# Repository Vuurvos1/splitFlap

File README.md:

<h1 align="center">SplitFlap</h1>

<p align="center">A modernized split flap display.</p>

## Features

- 50 Flaps per module
- 54mm x 80mm Character size
- Compact 80mm x 160mm x 110mm module size
- 3D printable
- Daisy chained
- Web controllabe

## Dashboard

The display can be controlled through a web dashboard hosted on the controller module.

## Flap Characters

Suggested 50 characters:

```
A B C D E F G H I J K L M N O P Q R S T U V W X Y Z (26)
1 2 3 4 5 6 7 8 9 0 (10)
blank □ full ■ (2)
? ! + - = * ' : , . @ # % € (14)
```

 <!-- $ & ^ ; -->

> [!NOTE]  
> `0 O` and `1 I` can share the same flap

## Materials

- 1x Nema 17 Stepper Motor
- 1x A4988 Stepper Motor Driver (or similar)
- 1x Hall Effect Switch (a TLE4905L or similar)
- 8x M3 Countersunk Screws (for the body)
- 8x M3 Screws (for the barrel)
- 4x M3x18 Screws (to mount the motor)
- 1x M3 Countersunk Screw (for the flap stopper)

### Micro controller

- Esp32
- Arduino pro micro

I am using an Esp32 for the main module, and you can use any other micro controller like a pro micro for the other modules.

### Motor

I originally got dual shafted Nema 17 motors for this project so I could mount the flap barrel on the back side of the motor.

> [!NOTE]  
> You could use any other Nema 17 motor with a reversed D shaft.
> Reversing the shaft can easily be done if you open up the motor and flip the shaft so it sticks out of the "back" of the motor.
> You might need to tweak the motor spacers and use different length screws to mount different motors.

### Driver

- A4988 Stepper Motor Driver

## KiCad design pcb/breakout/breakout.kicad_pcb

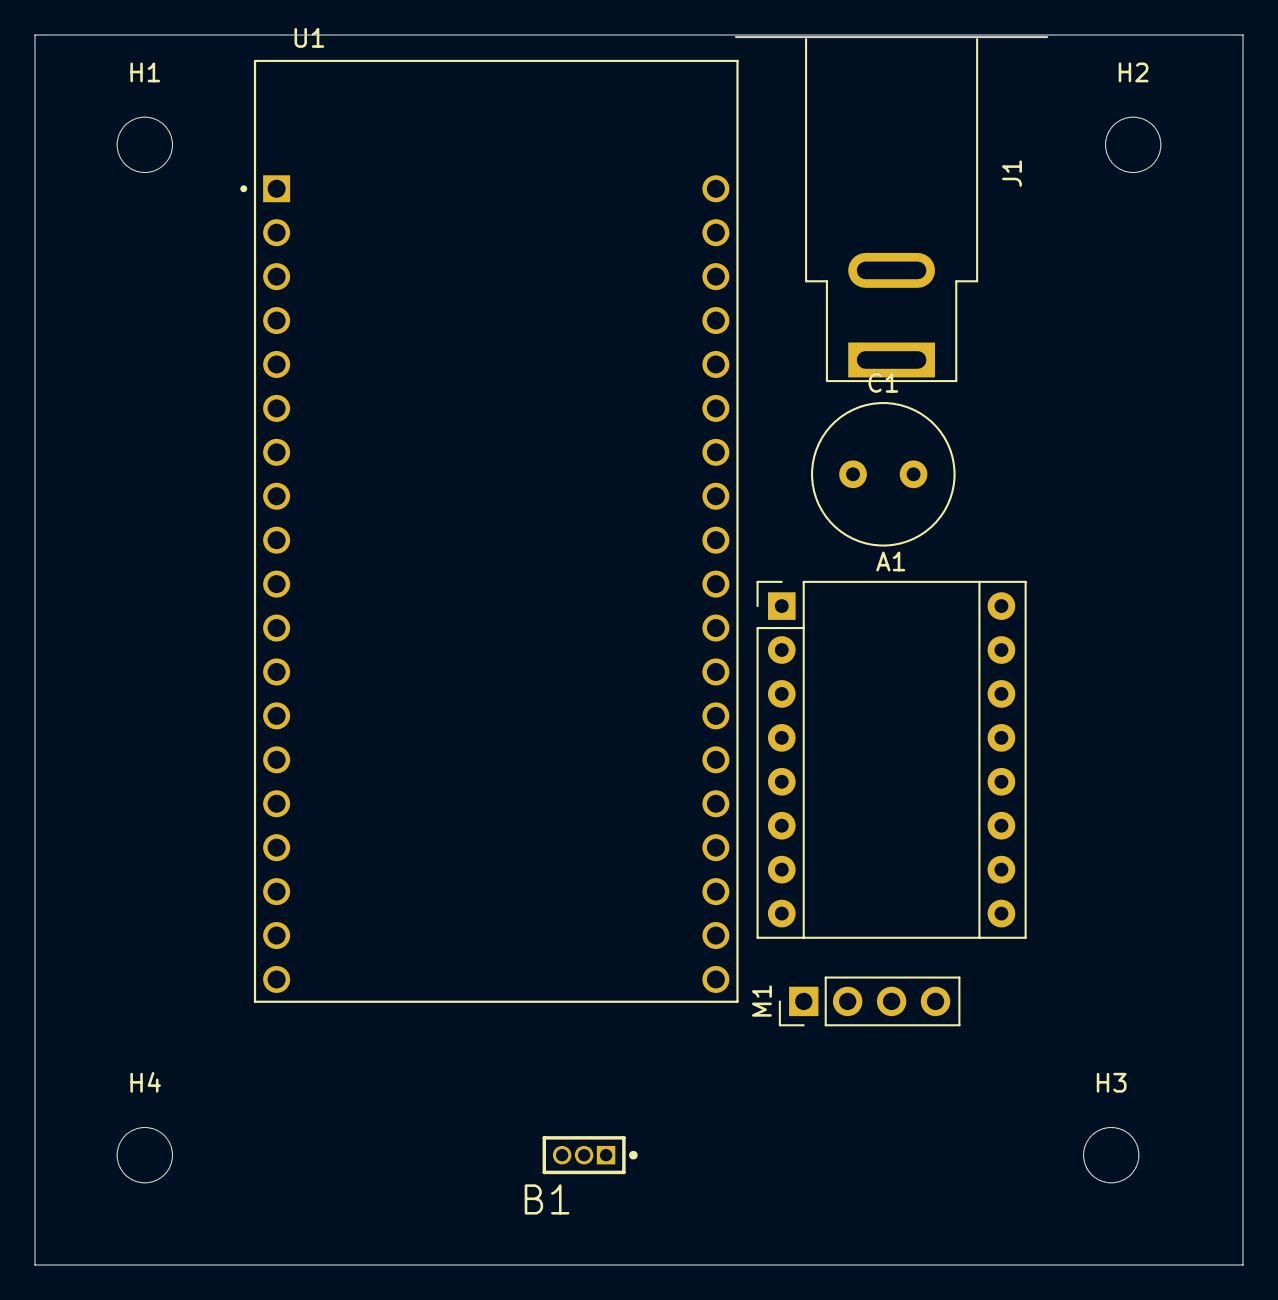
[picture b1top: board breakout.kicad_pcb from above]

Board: 2 copper layers, 69.8 x 71.0 mm, 10 parts (0 on the bottom side), 12 nets, no tracks yet.

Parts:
A1: Pololu_Breakout_A4988; Pololu_Breakout-16_15.2x20.3mm
B1: TLE4905L; IFX-PG-SSO-3-2
C1: 100uF; C_Radial_D8.0mm_H11.5mm_P3.50mm
H1, H2, H3, H4: MountingHole; MountingHole_3.2mm_M3
J1: Barrel_Jack; BarrelJack_SwitchcraftConxall_RAPC10U_Horizontal
M1: Stepper_Motor_bipolar; PinHeader_1x04_P2.54mm_Vertical
U1: ESP32-DEVKITC-32D; MODULE_ESP32-DEVKITC-32D

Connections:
+5V: A1.2 (VDD), A1.10 (MS1), A1.11 (MS2), A1.12 (MS3), B1.1 (VS)
+12V: A1.8 (VMOT), C1.1, J1.1
<NO NET>: A1.1 (GND), A1.7 (GND), C1.2, J1.2
D15: B1.3 (Q), U1.J3-16 (IO15)
D18: A1.15 (STEP), U1.J3-9 (IO18)
D19: A1.16 (DIR), U1.J3-8 (IO19)
GND: B1.2 (GND), U1.J2-14 (GND1), U1.J3-1 (GND3), U1.J3-7 (GND2)
unnamed: A1.4 (1A), M1.1
unnamed: A1.3 (1B), M1.2 (-)
unnamed: A1.5 (2A), M1.3
unnamed: A1.6 (2B), M1.4
unnamed: A1.13 (~RESET), A1.14 (~SLEEP)

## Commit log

2021-05-05 Tweaking barrel
2021-05-15 body and barrel tab
2021-05-22 Barrel tweaking
2021-05-23 Barrel width reduction
2021-05-29 Reworking assemblies and constraints
    Reworked constraints and assemblies, also tweaked barrel width to be a bit smaller so flaps don't fall out
2021-12-04 List characters to have on the split flap
2021-12-06 Beefing up barrel and tweeking sizes
2021-12-07 Rebuild and add possible special characters
2021-12-13 tweak barrel tolerances
2023-03-20 back mount motor
2023-03-20 add folder for code
2023-03-20 screwify barrel side
2023-03-21 change motor mounting
2023-03-21 update assemblies
2023-03-25 init code
2023-03-26 update mounting
2023-03-27 update barrel holes
2023-03-29 logic scaffolding
2023-03-29 updating to new stepper motor
2023-03-30 adding bolts
2023-04-03 update readme and add possible stepper libraries
2023-04-05 make stepper do turn
2024-05-09 working on module body
2024-05-14 working on body
2024-05-14 Making motors turn
2024-05-16 setup web server
2024-05-19 basic set flap logic
2024-05-19 winder thing
2024-05-19 use accell stepper lib
2024-06-19 upper case characters
2024-07-21 feat: move splitflap logic
2025-04-12 moving mcu code
2025-04-12 remove file
2025-04-12 test ci
2025-04-12 update ci
2025-04-12 fix config fild
2025-04-13 share data over uart
2025-04-13 fix packet order
2025-04-14 forwarding packets
2025-04-14 chore: remove generated files
2025-04-14 speed up forwarding of packets
2025-04-14 fix typo
2025-04-15 add flap code to module
2025-04-16 tweaking models
2025-04-17 file cleaning
2025-04-22 update model
2025-04-22 basic homing and testing logic
2025-04-24 add module image to readme
2025-04-25 improve homing logic
2025-04-25 fix: homing logic and set flap overflow
2025-04-26 feat: setup svelte dashboard
2025-04-26 feat: serve dashboard on esp
2025-04-26 try out freecad
2025-04-28 stuff
2025-04-29 improve grid
2025-04-29 fix filename
2025-04-29 send data to esp
2025-05-03 update cad
2025-05-04 improve modeling
2025-05-12 remove old cad files
2025-05-14 fix: exploded assembly
2025-05-14 improve side cable routing
2025-05-16 tweak side chamfers and routing
2025-05-18 add wireing schematic
2025-05-18 update pinout
2025-05-19 update favicon
2025-05-19 chore: remove test code
